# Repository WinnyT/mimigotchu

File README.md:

# Mimigotchu: a non-distractible reminder
This pet will help me reduce my screen time by playing hide-and-seek with me, so I can stay away from my phone! To be specific, they will play sound when I was doing a task for too long and run away so have to stand up and find them. Potential turn into a stress reliever.

# How to build
1. 3D print the pet case and wheels
2. Solder all the component of the PCB on to the PCB
   1. XIAO ESP32-C6 (SMD, center of board)
   2. L293D motor driver (U3)
   3. OLED header pins (U2)
   4. Buttons SW1, SW2, SW3
   5. Buzzer (BUZZER1)
   6. Battery connector (BT1)
   7. Motor connector (M1)
4. Screw the PCB on to the upper case using the M3 bolt 
5. Put on the rubber band to the wheels
6. Place the motor on the **Right Bottom** corner, it should fit the motor holder case
7. Put the stick in between the hole. **THEN** put on the wheels. Do the same for both front and back
8. Snap 2 case todether and connect the pet to your computer with a type-c cable
9. Download the firmware file and upload it to XIAO ESP32

# How to use
There are 3 buttons from LEFT to RIGHT. I'll call them Left - Middle - Right

Left Button: 
Short press - +1 minute

Middle Button: 
Short press - +1 second

Right Button:
Short press - Start countdown
Long press - Switch to pet screen

Left & Middle Button - Reset Timer

Oled screen:
Timer mode: showing countdown of the timer MM:SS
Pet mode: showing hapiness and age

**MIMI will run away when the timer is UP**

# Why I make this
I found myself addicted to phone, and I have tried many ways to reduce my screen time like set a timer or use a timer lock down. But it never work. The problem I found with setting a timer is I leave it by my side, so it was too easy for me to turn it off and not getting away from my phone. I hope this robot can run away, make me stand up and catch them. _Sounds silly but what if it works ?.?_

# CAD 

[Link](https://cad.onshape.com/documents/3b2edbb59c71210e96e39001/w/2137fb4aa4ad6a67b537fdc8/e/cc7023662d27975941fd0b95?renderMode=0&uiState=6a374ef8deeac3007e5d66ae) to Onshape design. 

# PCB

[Download gebber file](https://github.com/WinnyT/mimigotchu/blob/main/assets/pcb/gebber/gebber.zip)
### 3D view of the PCB

Front

Back

### 3D model after assembly the PCB
Front

Back

### Schematic

# Firmware

You can flash Mimigotchi without installing PlatformIO.

[Download latest firmware](https://github.com/WinnyT/mimigotchu/releases/tag/v1.0.1)

### Flash instructions (macOS/Windows/Linux)
1. Install [esptool](https://docs.espressif.com/projects/esptool/en/latest/) via terminal:

pip install esptool

2. Connect your Mimigotchi via USB-C
3. Download `bootloader.bin`, `partitions.bin`, and `firmware.bin` from the release
4. Run (from the folder containing all three files):
esptool.py --port /dev/tty.usbmodem* write_flash 

0x0     bootloader.bin 

0x8000  partitions.bin 

0x10000 firmware.bin
   On Windows, replace `/dev/tty.usbmodem*` with `COM3`
   
### Build from source
If you want to modify the code, open the project in VS Code with PlatformIO installed and press `Ctrl+Alt+B` to build, then `Ctrl+Alt+U` to upload.

# BOM
Check out `mimigotchu_bom.csv` or [this](https://docs.google.com/spreadsheets/d/1_V7xxnciXNeib1qt1jn1ameioscYv5FXHhLbUMrxZ48/edit?usp=sharing) link.

# Easter Egg
If you finished a study session ( 50+ minutes) your pet will be happier !!

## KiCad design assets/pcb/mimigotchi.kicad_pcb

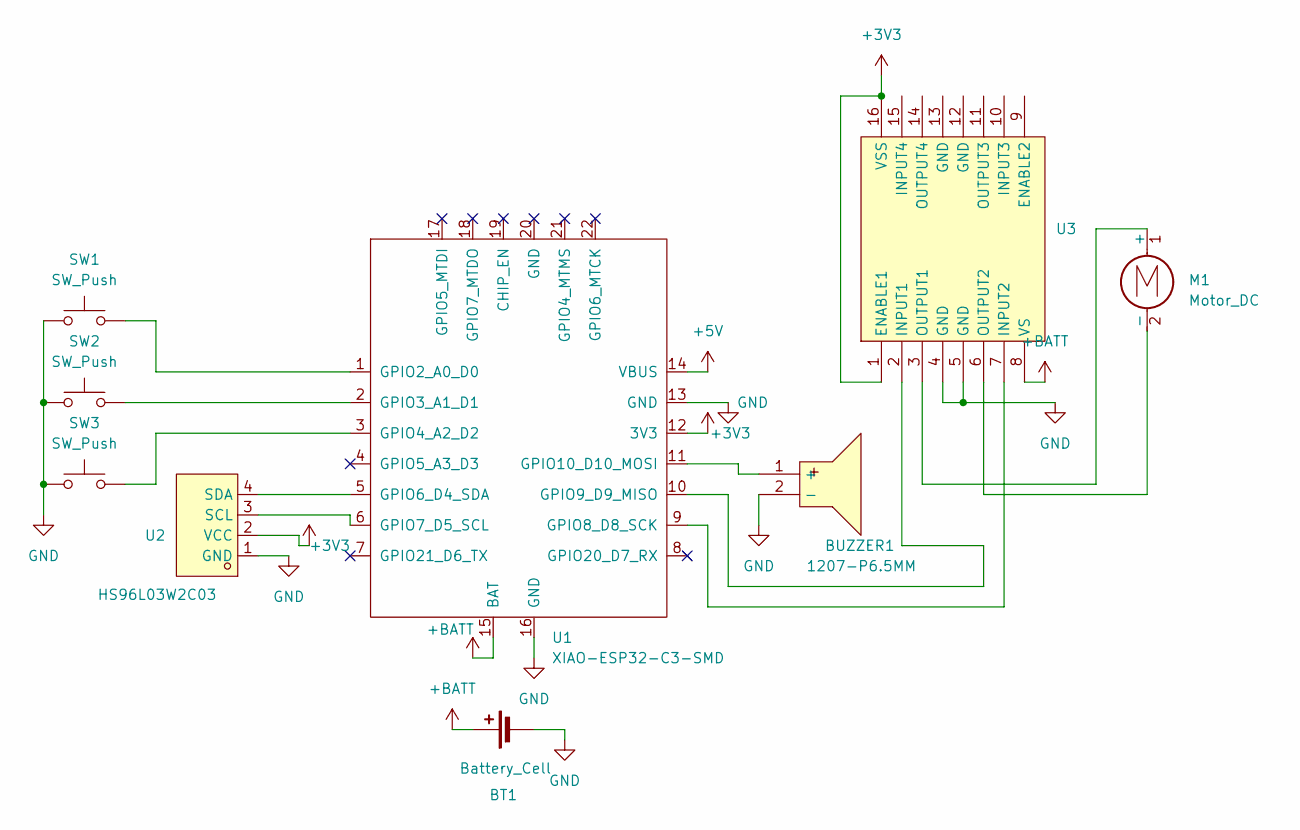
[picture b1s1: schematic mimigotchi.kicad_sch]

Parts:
BT1: Battery_Cell; PinHeader_1x02_P2.54mm_Vertical
BUZZER1: 1207-P6.5MM; BUZ-TH_BD12.5-P6.50-D1.4; MPN 1207-P6.5MM; LCSC Part C49246964
M1: Motor_DC; PinHeader_1x02_P2.54mm_Vertical
SW1, SW2, SW3: SW_Push; SW-TH_4P-L4.5-W4.5-P3.00-LS4.8
U1: XIAO-ESP32-C3-SMD
U2: HS96L03W2C03; OLED-TH_L27.8-W27.2-P2.54_C9900033791; MPN HS96L03W2C03; LCSC Part C5248080
U3: L293D; DIP-16_L20.0-W6.4-P2.54-LS7.6-BL; MPN L293D; LCSC Part C12340

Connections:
+3V3: U1.12 (3V3), U2.2 (VCC), U3.1 (ENABLE1), U3.16 (VSS)
+5V: U1.14 (VBUS)
+BATT: BT1.1 (+), U1.15 (BAT), U3.8 (VS)
GND: BT1.2 (-), BUZZER1.2 (-), SW1.1, SW2.1, SW3.1, U1.13 (GND), U1.16 (GND), U2.1 (GND), U3.4 (GND), U3.5 (GND)
unnamed: BUZZER1.1 (+), U1.11 (GPIO10_D10_MOSI)
unnamed: M1.1 (+), U3.3 (OUTPUT1)
unnamed: M1.2 (-), U3.6 (OUTPUT2)
unnamed: SW1.2, U1.1 (GPIO2_A0_D0)
unnamed: SW2.2, U1.2 (GPIO3_A1_D1)
unnamed: SW3.2, U1.3 (GPIO4_A2_D2)
unnamed: U1.5 (GPIO6_D4_SDA), U2.4 (SDA)
unnamed: U1.6 (GPIO7_D5_SCL), U2.3 (SCL)
unnamed: U1.9 (GPIO8_D8_SCK), U3.7 (INPUT2)
unnamed: U1.10 (GPIO9_D9_MISO), U3.2 (INPUT1)

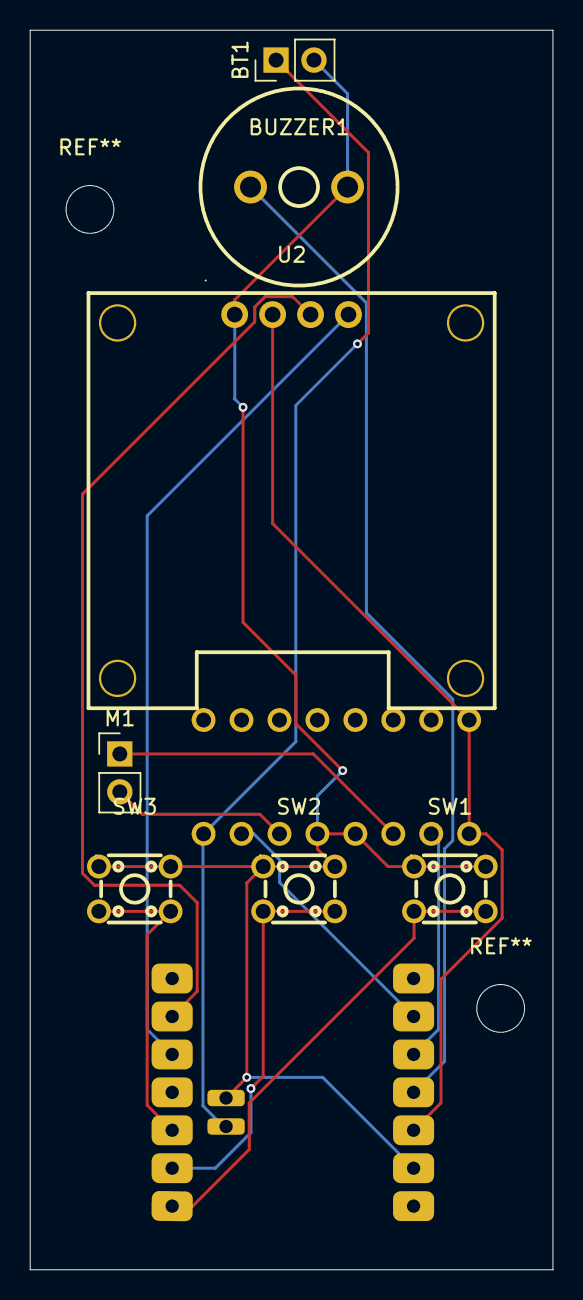
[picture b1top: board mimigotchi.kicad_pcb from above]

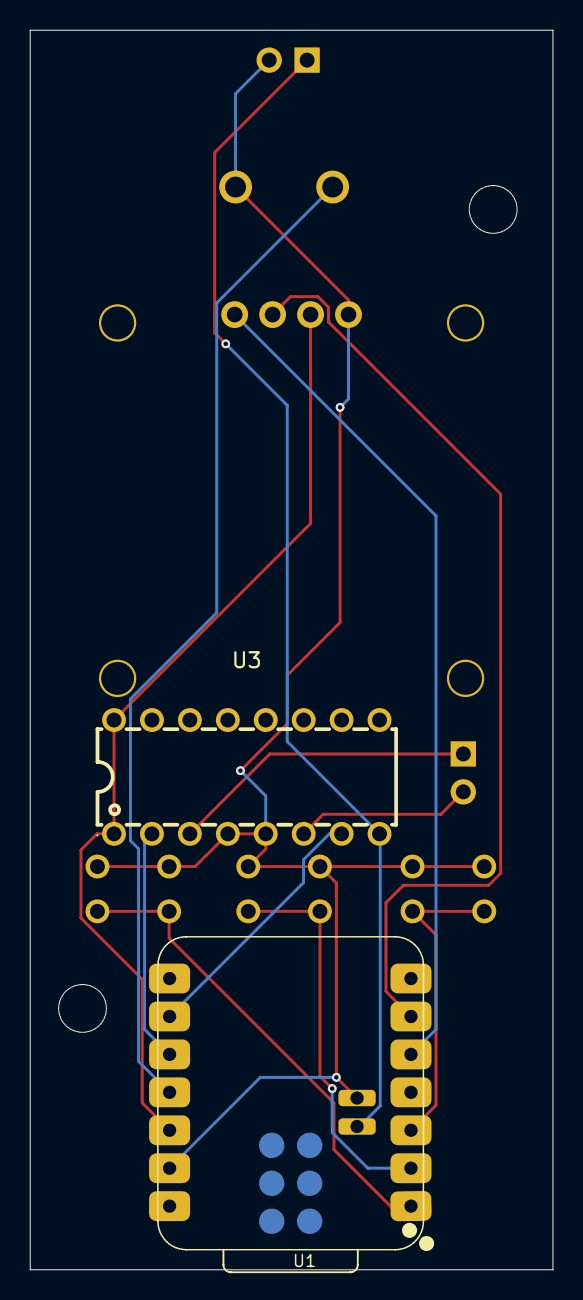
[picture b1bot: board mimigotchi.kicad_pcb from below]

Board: 2 copper layers, 35.0 x 83.0 mm, 9 parts (2 on the bottom side), 13 nets.

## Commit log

2026-06-07 Enhance README formatting and content clarity
    Updated README.md to improve formatting and clarity.
2026-06-11 Rename Mimigotchu.pdf to docs/mimigotchu zine page.pdf
2026-06-11 Rename mimigotchi.kicad_pcb to assets/pcb/mimigotchi.kicad_pcb
2026-06-11 Rename mimigotchi.kicad_pro to assets/pcb/mimigotchi.kicad_pro
2026-06-11 Rename mimigotchi.kicad_sch to assets/pcb/mimigotchi.kicad_sch
2026-06-11 Rename mimigotchu.step to assets/mimigotchu.step
2026-06-11 Update README with name correction and additional info
    Corrected the project name and improved some phrasing in the README. Added a firmware section and clarified assembly instructions.
2026-06-13 Revise README with button actions and firmware details
    Updated button functions and added firmware flashing instructions.
2026-06-13 Revise firmware download and flashing steps
    Updated firmware download link and flashing instructions.
2026-06-13 Rename Mimigotchu - Sheet1.csv to boms/Mimigotchu_bom.csv
2026-06-13 Rename mimigotchi.kicad_pcb to mimigotchu.kicad_pcb
2026-06-13 Rename mimigotchi.kicad_sch to mimigotchu.kicad_sch
2026-06-13 Rename mimigotchi.kicad_pro to mimigotchu.kicad_pro
2026-06-14 Add new image and enhance project description
    Updated the README to include a new image and improved description.
2026-06-14 Rename Mimigotchu.pdf to docs/mimigotchu_zine.pdf
2026-06-14 Rename platformio.ini to src/platformio.ini
2026-06-14 Rename sdkconfig.defaults to scr/sdkconfig.defaults
2026-06-17 Rename Assembly 1.step to assets/mimigotchu.step
2026-06-17 Rename assets/pcb/gebber.zip to assets/pcb/gebber/gebber.zip
2026-06-17 Add download link for gebber file
    Added download link for gebber file in PCB section.
2026-06-17 Rename assets/bottom_case.step to assets/cad/bottom_case.step
2026-06-17 Rename assets/top_case.step to assets/cad/top_case.step
2026-06-17 Enhance README with CAD and PCB details
    Added images and sections for PCB and CAD in README.
2026-06-19 Update Onshape design link in README
2026-06-19 Replace image in README with new asset
    Updated image in README.md to a new asset.
2026-06-19 Replace image in README with new asset
    Updated image in README and improved formatting.
2026-06-19 Rename Mimigotchu (1).pdf to mimigotchu_zine.pdf
2026-06-19 Replace old image with new pet image
    Updated image source in README for the pet project.
2026-06-19 Rename Mimigotchu (2).pdf to mimigotchu_zine.pdf
2026-06-21 Rename file from Sheet1.csv to mimigotchu_bom.csv
2026-06-23 Replace image in README with new asset
    Updated the image in the README to a new asset.
2026-06-23 Rename Mimigotchu.pdf to mimigotchu_zine.pdf
